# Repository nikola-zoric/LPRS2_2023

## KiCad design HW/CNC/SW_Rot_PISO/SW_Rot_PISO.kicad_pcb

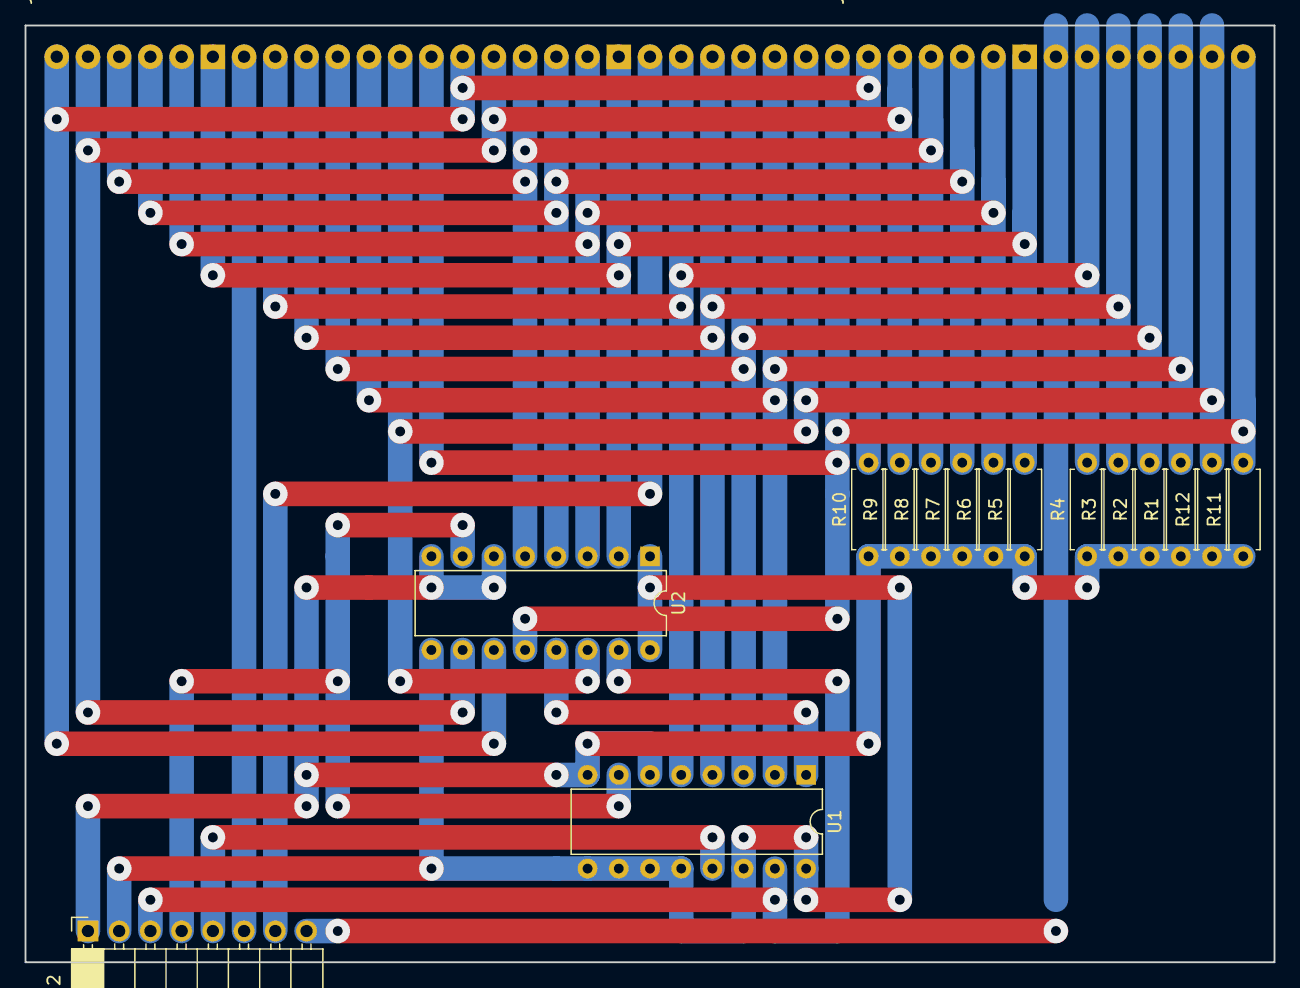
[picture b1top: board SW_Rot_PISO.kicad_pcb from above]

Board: 2 copper layers, 101.6 x 76.2 mm, 18 parts (1 on the bottom side), 21 nets.

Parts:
J1, J3, J4: 1x13 2.54mm male 90deg; SW_Rot_1x12_Daughterbrd_Conn
J2: 1x8 2.54mm female 90deg; PinSocket_1x08_P2.54mm_Horizontal
R1, R2, R3, R4, R5, R6, R7, R8, R9, R10, R11, R12: 1k; R_Axial_DIN0207_L6.3mm_D2.5mm_P7.62mm_Horizontal
U1, U2: 74LS166; DIP-16_W7.62mm

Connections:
/C00: J1.1, J3.1, J4.1, R5.2, U2.2 (A)
/C01: J1.2, J3.2, J4.2, R6.2, U2.3 (B)
/C02: J1.3, J3.3, J4.3, R7.2, U2.4 (C)
/C03: J1.4, J3.4, J4.4, R8.2, U2.5 (D)
/C04: J1.5, J3.5, J4.5, R9.2, U2.10 (E)
/C05: J1.6, J3.6, J4.6, R10.2, U2.11 (F)
/C06: J1.7, J3.7, J4.7, R11.2, U2.12 (G)
/C07: J1.8, J3.8, J4.8, R12.2, U2.14 (H)
/C08: J1.9, J3.9, J4.9, R1.2, U1.2 (A)
/C09: J1.10, J3.10, J4.10, R2.2, U1.3 (B)
/C10: J1.11, J3.11, J4.11, R3.2, U1.4 (C)
/C11: J1.12, J3.12, J4.12, R4.2, U1.5 (D)
/CLK: J2.4, U1.7 (Clk), U2.7 (Clk)
/DATA: J2.5, U1.13 (Qh)
/DATA1: U1.1 (Ds), U2.13 (Qh)
/N_LOAD: J2.3, U1.15 (PE), U2.15 (PE)
/R0: J1.13, J2.6
/R1: J2.7, J3.13
/R2: J2.8, J4.13
GND: J2.1, R1.1, R2.1, R3.1, R4.1, R5.1, R6.1, R7.1, R8.1, R9.1, R10.1, R11.1, R12.1, U1.6 (CE), U1.8 (GND), U2.6 (CE), U2.8 (GND)
VCC: J2.2, U1.9 (Clr), U1.10 (E), U1.11 (F), U1.12 (G), U1.14 (H), U1.16 (VCC), U2.1 (Ds), U2.9 (Clr), U2.16 (VCC)

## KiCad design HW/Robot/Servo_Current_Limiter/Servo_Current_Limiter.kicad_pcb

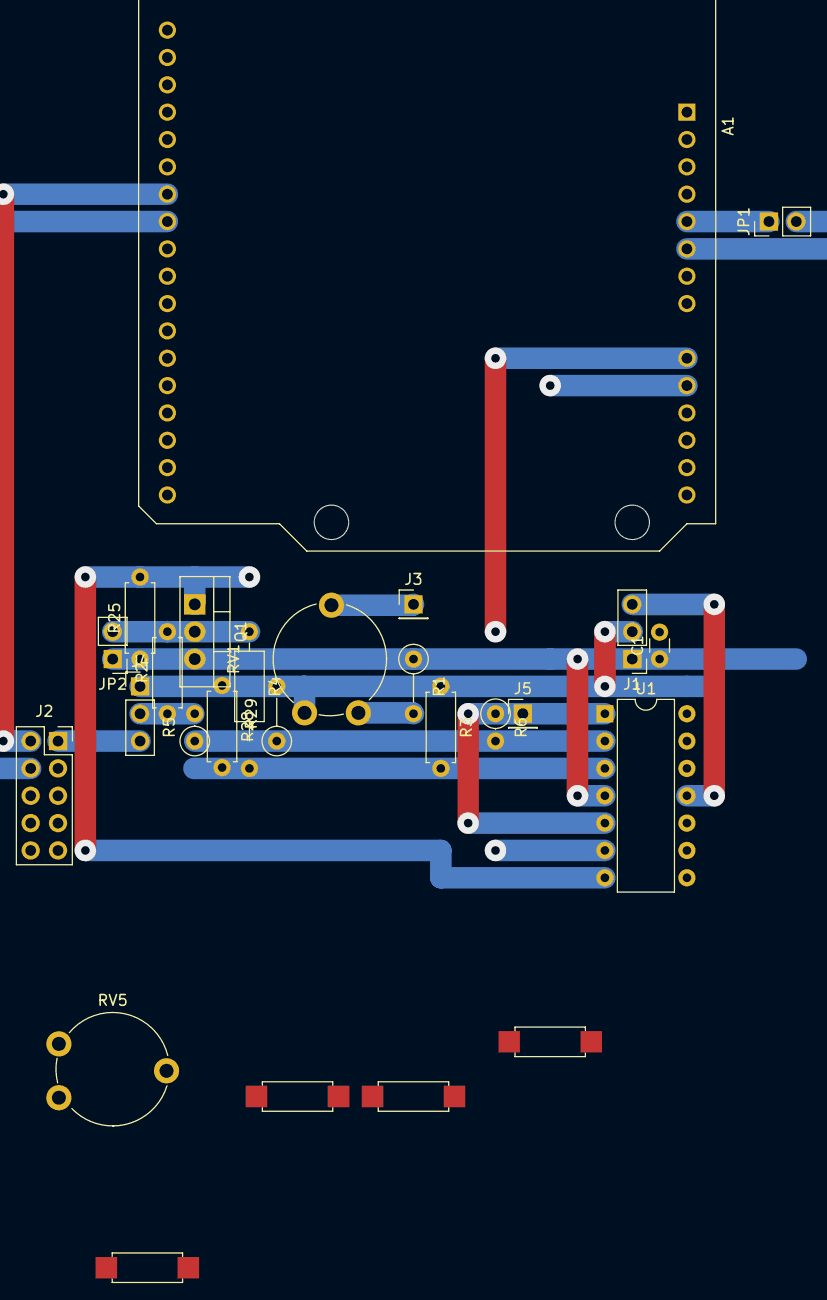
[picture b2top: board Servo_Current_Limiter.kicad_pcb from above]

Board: 2 copper layers, 26 parts (0 on the bottom side), 19 nets.

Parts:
A1: Arduino_UNO_R3; Arduino_UNO_R3_WithMountingHoles_Snapped_to_P2.54mm
C1: 100n; C_Disc_D3.0mm_W1.6mm_P2.50mm
J1, J4: 1x3 2.54mm male; PinHeader_1x03_P2.54mm_Vertical
J2: Conn_02x05_Odd_Even; PinSocket_2x05_P2.54mm_Vertical
J3, J5: 1x1 2.54mm male; PinHeader_1x01_P2.54mm_Vertical
JP1, JP2: 1x2 2.54mm male; PinHeader_1x02_P2.54mm_Vertical
Q1: IRF4905; TO-220-3_Vertical
R1: 1k; R_Axial_DIN0207_L6.3mm_D2.5mm_P5.08mm_Vertical
R2: 0.1; R_Axial_DIN0207_L6.3mm_D2.5mm_P7.62mm_Horizontal
R3, R25: 100k; R_Axial_DIN0207_L6.3mm_D2.5mm_P7.62mm_Horizontal
R4: 10k; R_Axial_DIN0207_L6.3mm_D2.5mm_P12.70mm_Horizontal
R5: 10k; R_Axial_DIN0207_L6.3mm_D2.5mm_P2.54mm_Vertical
R6: 100k; R_Axial_DIN0207_L6.3mm_D2.5mm_P2.54mm_Vertical
R7, R30: 1k; R_Axial_DIN0207_L6.3mm_D2.5mm_Pinf_Horizontal
R26, R27: 10k; R_Axial_DIN0207_L6.3mm_D2.5mm_Pinf_Horizontal
R28: 10k; R_Axial_DIN0207_L6.3mm_D2.5mm_P7.62mm_Horizontal
R29: 10k; R_Axial_DIN0207_L6.3mm_D2.5mm_P5.08mm_Vertical
RV1, RV5: 1k; Potentiometer_Piher_PT-10-V10_Vertical
U1: LM324; DIP-14_W7.62mm

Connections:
+5V: C1.1, J1.1, JP1.2 (B), JP2.1 (A), Q1.3 (S), R1.1, R25.1, R26.1, U1.4 (V+)
-5V: C1.2, J1.3, U1.11 (V-)
/ARD_PWM0: A1.26 (D11), J2.2
/ARD_PWM1: A1.25 (D10), J2.4
/ARD_PWM2: A1.24 (D9), J2.6
/ARD_PWM3: A1.20 (D5), J2.8
/DIS0: A1.17 (D2), J3.1, RV1.2, U1.6 (-)
/OUT0: A1.9 (A0), J5.1, R6.1, R30.1, U1.1, U1.5 (+)
/PWM0: J2.1, J4.3
/ch0/CTRL: Q1.1 (G), R7.1, R25.2, U1.7
/ch0/N: J4.2, R2.1, R5.2
/ch0/P: JP2.2 (B), Q1.2 (D), R2.2, R4.1, RV5.2
GND: A1.6 (GND), A1.7 (GND), J1.2, J2.9, J2.10, J4.1, R3.1, R7.2, R27.2, R28.1, R29.2, R30.2, RV1.3
unnamed: A1.5 (+5V), JP1.1 (A)
unnamed: R1.2, RV1.1
unnamed: R26.2, RV5.1
unnamed: R27.1, RV5.3
unnamed: R3.2, R4.2, R28.2, U1.3 (+)
unnamed: R5.1, R6.2, R29.1, U1.2 (-)

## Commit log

2023-06-03 Something done.
2023-06-06 Working.
2023-06-08 Corrections.
2023-06-08 Test FW.
2023-06-08 Solution for offset. Now it works.
2023-06-08 Plan.
2023-06-08 One board done.
2023-06-12 Correction.
2023-06-13 Corrections after soldering prototype.
2023-06-13 Laser cutting holes.
2023-06-15 Temperature recorder created.
2023-06-15 added README file
2023-06-15 Changes on ReadMe
